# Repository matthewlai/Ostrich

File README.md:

# Ostrich
STM32F7 middleware library and development board.

# Size Notes
* Any std::istream/std::ostream instantiation (including including \<iostream\>) (~140KB)
* Floating point I/O support through libostrich streams (~10KB)
* Floating point scanf/printf support (~20KB)

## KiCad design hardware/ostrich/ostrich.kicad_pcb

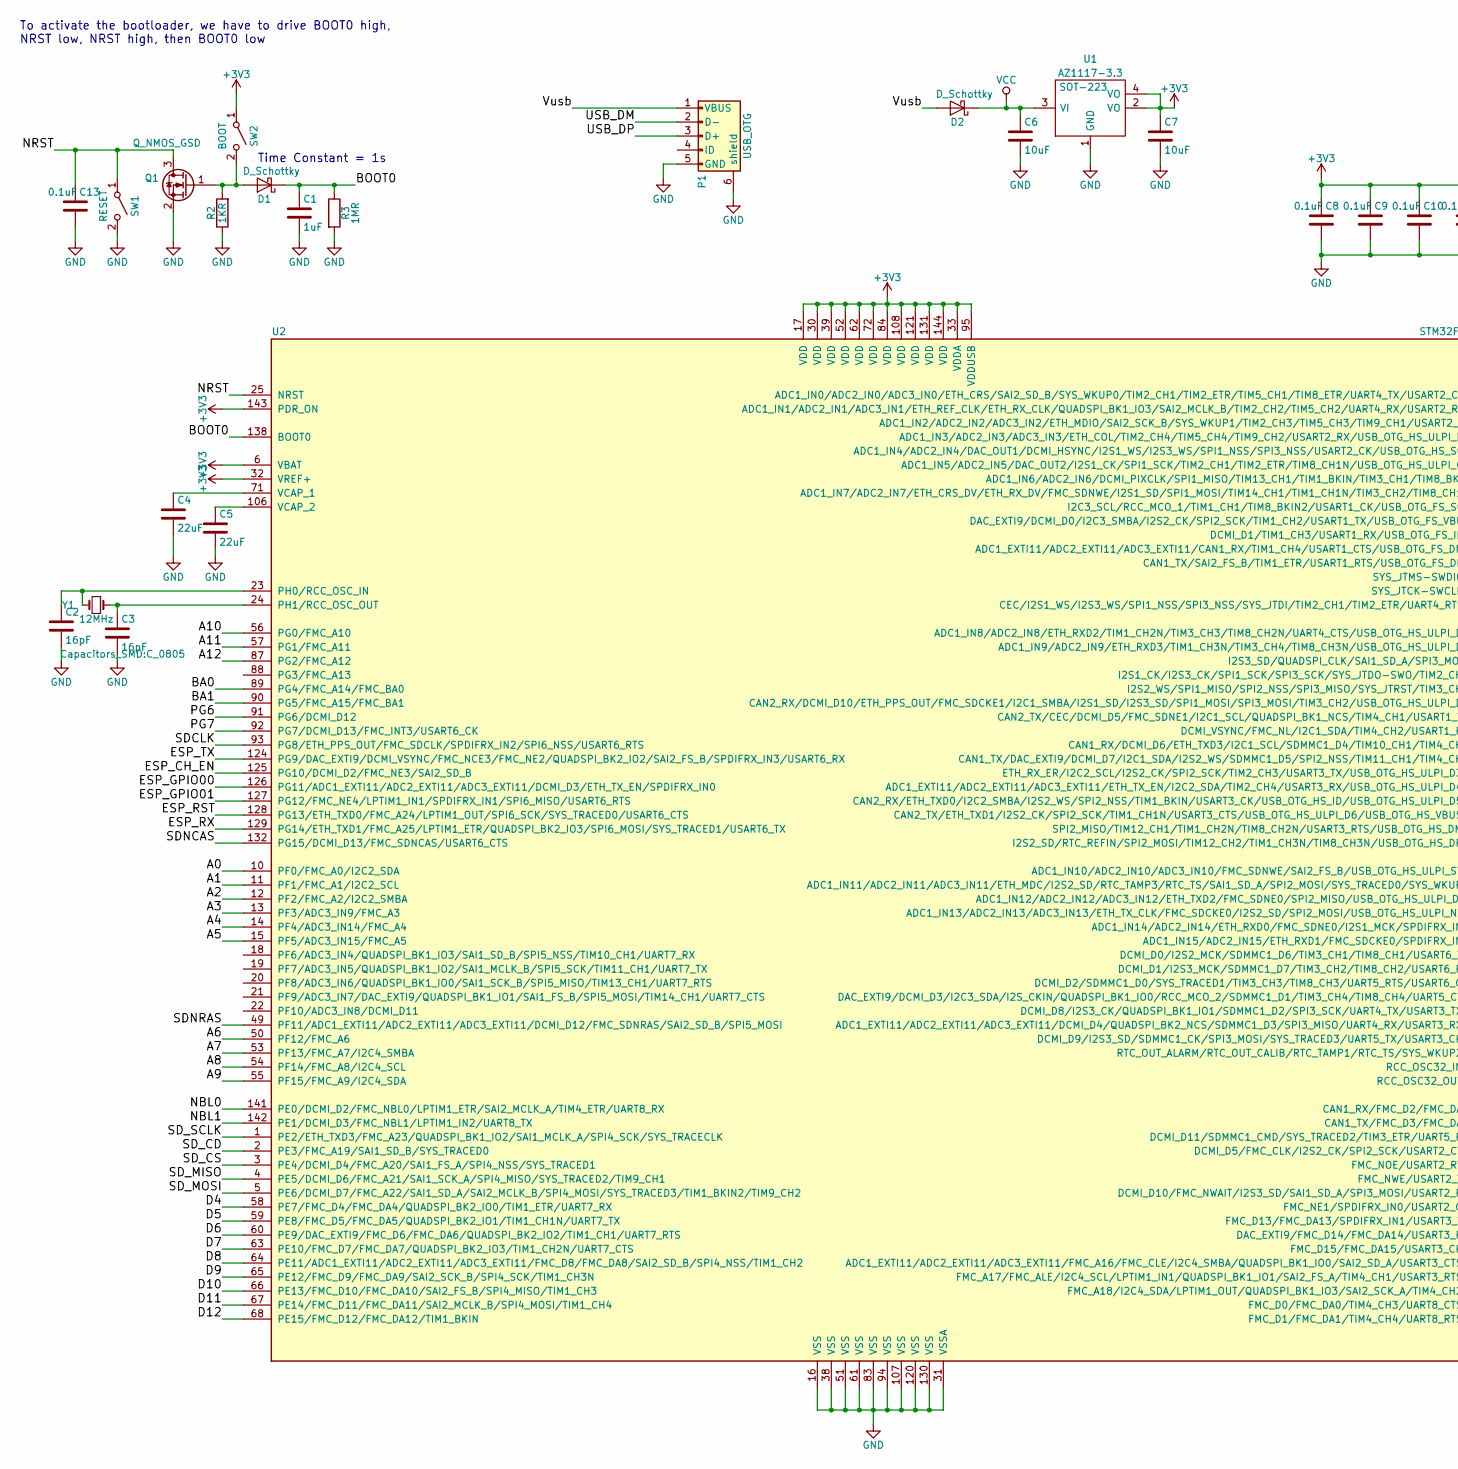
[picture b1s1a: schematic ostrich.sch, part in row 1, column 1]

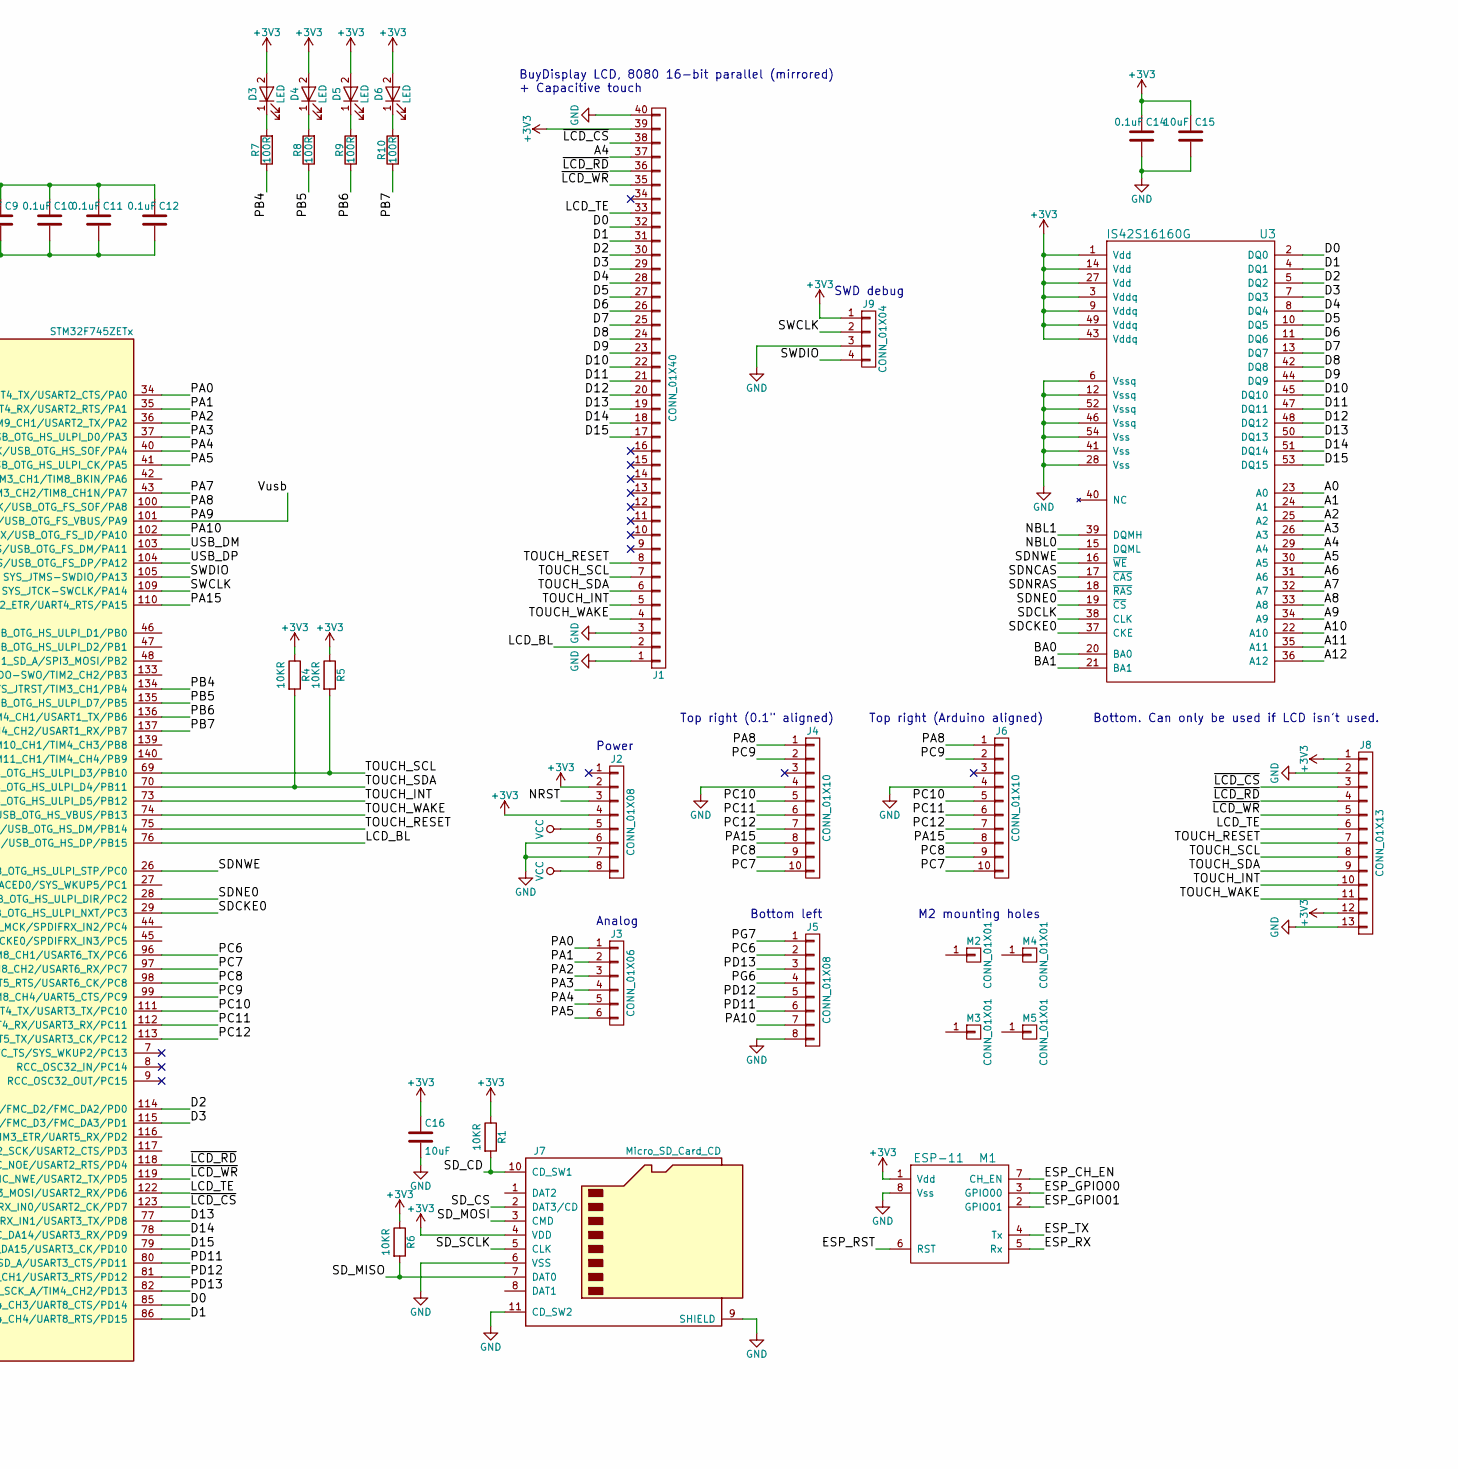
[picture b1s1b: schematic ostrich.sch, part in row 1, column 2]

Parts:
C1: 1uF; C_0805
C2, C3: 16pF; C_0805
C4, C5: 22uF; C_0805
C6, C7, C15, C16: 10uF; C_0805
C8, C9, C10, C11, C12, C13, C14: 0.1uF; C_0805
D1, D2: D_Schottky; D_1206
D3, D4, D5, D6: LED; LED_0805
J1: CONN_01X40; ER-CON40HB-2
J2, J5: CONN_01X08; Pin_Header_Straight_1x08_Pitch2.54mm
J3: CONN_01X06; Pin_Header_Straight_1x06_Pitch2.54mm
J4, J6: CONN_01X10; Pin_Header_Straight_1x10_Pitch2.54mm
J7: Micro_SD_Card_CD; Amphenol_1140084168
J8: CONN_01X13; Pin_Header_Straight_1x13_Pitch2.54mm
J9: CONN_01X04; Pin_Header_Straight_1x04_Pitch2.54mm
M1: ESP-11
M2, M3, M4, M5: CONN_01X01; M2_HOLE
P1: USB_OTG; USB_Micro-B_Molex_47346-0001_HS
Q1: Q_NMOS_GSD; SOT-23
R1, R4, R5, R6: 10KR; R_0805
R2: 1KR; R_0805
R3: 1MR; R_0805
R7, R8, R9, R10: 100R; R_0805
SW1: RESET; LL3301NF065QG
SW2: BOOT; LL3301NF065QG
U1: AZ1117-3.3; SOT-223
U2: STM32F745ZETx; LQFP-144_20x20mm_Pitch0.5mm
U3: IS42S16160G; TSOPII-54_10.16x22.22mm-Pitch0.8mm
Y1: 12MHz; Crystal_SMD_Abracon_ABM3-2pin_5.0x3.2mm_HandSoldering

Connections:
+3V3: C7.1, C8.1, C9.1, C10.1, C11.1, C12.1, C14.1, C15.1, C16.1, D3.2 (A), D4.2 (A), D5.2 (A), D6.2 (A), J1.39, J2.2, J2.4, J7.4 (VDD), J8.1, J8.12, J9.1, M1.1 (Vdd), R1.1, R4.1, R5.1, R6.1, SW2.1 (A), U1.2 (VO), U1.4 (VO), U2.6 (VBAT), U2.17 (VDD), U2.30 (VDD), U2.32 (VREF+), U2.33 (VDDA), U2.39 (VDD), U2.52 (VDD), U2.62 (VDD), U2.72 (VDD), U2.84 (VDD), U2.95 (VDDUSB), U2.108 (VDD), U2.121 (VDD), U2.131 (VDD), U2.143 (PDR_ON), U2.144 (VDD), U3.1 (Vdd), U3.3 (Vddq), U3.9 (Vddq), U3.14 (Vdd), U3.27 (Vdd), U3.43 (Vddq), U3.49 (Vddq)
/A0: U2.10 (PF0/FMC_A0/I2C2_SDA), U3.23 (A0)
/A1: U2.11 (PF1/FMC_A1/I2C2_SCL), U3.24 (A1)
/A2: U2.12 (PF2/FMC_A2/I2C2_SMBA), U3.25 (A2)
/A3: U2.13 (PF3/ADC3_IN9/FMC_A3), U3.26 (A3)
/A4: J1.37, U2.14 (PF4/ADC3_IN14/FMC_A4), U3.29 (A4)
/A5: U2.15 (PF5/ADC3_IN15/FMC_A5), U3.30 (A5)
/A6: U2.50 (PF12/FMC_A6), U3.31 (A6)
/A7: U2.53 (PF13/FMC_A7/I2C4_SMBA), U3.32 (A7)
/A8: U2.54 (PF14/FMC_A8/I2C4_SCL), U3.33 (A8)
/A9: U2.55 (PF15/FMC_A9/I2C4_SDA), U3.34 (A9)
/A10: U2.56 (PG0/FMC_A10), U3.22 (A10)
/A11: U2.57 (PG1/FMC_A11), U3.35 (A11)
/A12: U2.87 (PG2/FMC_A12), U3.36 (A12)
/BA0: U2.89 (PG4/FMC_A14/FMC_BA0), U3.20 (BA0)
/BA1: U2.90 (PG5/FMC_A15/FMC_BA1), U3.21 (BA1)
/BOOT0: C1.1, D1.1 (K), R3.1, U2.138 (BOOT0)
/D0: J1.32, U2.85 (FMC_D0/FMC_DA0/TIM4_CH3/UART8_CTS/PD14), U3.2 (DQ0)
/D1: J1.31, U2.86 (FMC_D1/FMC_DA1/TIM4_CH4/UART8_RTS/PD15), U3.4 (DQ1)
/D2: J1.30, U2.114 (CAN1_RX/FMC_D2/FMC_DA2/PD0), U3.5 (DQ2)
/D3: J1.29, U2.115 (CAN1_TX/FMC_D3/FMC_DA3/PD1), U3.7 (DQ3)
/D4: J1.28, U2.58 (PE7/FMC_D4/FMC_DA4/QUADSPI_BK2_IO0/TIM1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), U3.8 (DQ4)
/D5: J1.27, U2.59 (PE8/FMC_D5/FMC_DA5/QUADSPI_BK2_IO1/TIM1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), U3.10 (DQ5)
/D6: J1.26, U2.60 (PE9/DAC_EXTI9/FMC_D6/FMC_DA6/QUADSPI_BK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), U3.11 (DQ6)
/D7: J1.25, U2.63 (PE10/FMC_D7/FMC_DA7/QUADSPI_BK2_IO3/TIM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), U3.13 (DQ7)
/D8: J1.24, U2.64 (PE11/ADC1_EXTI11/ADC2_EXTI11/ADC3_EXTI1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), U3.42 (DQ8)
/D9: J1.23, U2.65 (PE12/FMC_D9/FMC_DA9/SAI2_SCK_B/SPI4_SCK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), U3.44 (DQ9)
/D10: J1.22, U2.66 (PE13/FMC_D10/FMC_DA10/SAI2_FS_B/SPI4_MI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), U3.45 (DQ10)
/D11: J1.21, U2.67 (PE14/FMC_D11/FMC_DA11/SAI2_MCLK_B/SPI4_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), U3.47 (DQ11)
/D12: J1.20, U2.68 (PE15/FMC_D12/FMC_DA12/TIM1_BKIN), U3.48 (DQ12)
/D13: J1.19, U2.77 (FMC_D13/FMC_DA13/SPDIFRX_IN1/USART3_TX/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), U3.50 (DQ13)
/D14: J1.18, U2.78 (DAC_EXTI9/FMC_D14/FMC_DA14/USART3_RX/PD9), U3.51 (DQ14)
/D15: J1.17, U2.79 (FMC_D15/FMC_DA15/USART3_CK/PD10), U3.53 (DQ15)
/ESP_CH_EN: M1.7 (CH_EN), U2.125 (PG10/DCMI_D2/FMC_NE3/SAI2_SD_B)
/ESP_GPIO00: M1.3 (GPIO00), U2.126 (PG11/ADC1_EXTI11/ADC2_EXTI11/ADC3_EXTI1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)
/ESP_GPIO01: M1.2 (GPIO01), U2.127 (PG12/FMC_NE4/LPTIM1_IN1/SPDIFRX_IN1/SPI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)
/ESP_RST: M1.6 (RST), U2.128 (PG13/ETH_TXD0/FMC_A24/LPTIM1_OUT/SPI6_S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)
/ESP_RX: M1.5 (Rx), U2.129 (PG14/ETH_TXD1/FMC_A25/LPTIM1_ETR/QUADSP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)
/ESP_TX: M1.4 (Tx), U2.124 (PG9/DAC_EXTI9/DCMI_VSYNC/FMC_NCE3/FMC_N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)
/LCD_BL: J1.2, U2.76 (I2S2_SD/RTC_REFIN/SPI2_MOSI/TIM12_CH2/T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)
/LCD_TE: J1.33, J8.6, U2.122 (DCMI_D10/FMC_NWAIT/I2S3_SD/SAI1_SD_A/SP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)
/NBL0: U2.141 (PE0/DCMI_D2/FMC_NBL0/LPTIM1_ETR/SAI2_MC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), U3.15 (DQML)
/NBL1: U2.142 (PE1/DCMI_D3/FMC_NBL1/LPTIM1_IN2/UART8_TX), U3.39 (DQMH)
/NRST: C13.1, J2.3, Q1.3 (D), SW1.1 (A), U2.25 (NRST)
/PA0: J3.1, U2.34 (ADC1_IN0/ADC2_IN0/ADC3_IN0/ETH_CRS/SAI2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)
/PA1: J3.2, U2.35 (ADC1_IN1/ADC2_IN1/ADC3_IN1/ETH_REF_CLK/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)
/PA2: J3.3, U2.36 (ADC1_IN2/ADC2_IN2/ADC3_IN2/ETH_MDIO/SAI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)
/PA3: J3.4, U2.37 (ADC1_IN3/ADC2_IN3/ADC3_IN3/ETH_COL/TIM2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)
/PA4: J3.5, U2.40 (ADC1_IN4/ADC2_IN4/DAC_OUT1/DCMI_HSYNC/I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)
/PA5: J3.6, U2.41 (ADC1_IN5/ADC2_IN5/DAC_OUT2/I2S1_CK/SPI1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)
/PA7: U2.43 (ADC1_IN7/ADC2_IN7/ETH_CRS_DV/ETH_RX_DV/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)
/PA8: J4.1, J6.1, U2.100 (I2C3_SCL/RCC_MCO_1/TIM1_CH1/TIM8_BKIN2/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)
/PA9: D2.2 (A), P1.1 (VBUS), U2.101 (DAC_EXTI9/DCMI_D0/I2C3_SMBA/I2S2_CK/SPI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)
/PA10: J5.7, U2.102 (DCMI_D1/TIM1_CH3/USART1_RX/USB_OTG_FS_I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)
/PA15: J4.8, J6.8, U2.110 (CEC/I2S1_WS/I2S3_WS/SPI1_NSS/SPI3_NSS/S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)
/PB4: R7.1, U2.134 (I2S2_WS/SPI1_MISO/SPI2_NSS/SPI3_MISO/SY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)
/PB5: R8.1, U2.135 (CAN2_RX/DCMI_D10/ETH_PPS_OUT/FMC_SDCKE1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)
/PB6: R9.1, U2.136 (CAN2_TX/CEC/DCMI_D5/FMC_SDNE1/I2C1_SCL/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)
/PB7: R10.1, U2.137 (DCMI_VSYNC/FMC_NL/I2C1_SDA/TIM4_CH2/USA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)
/PC6: J5.2, U2.96 (DCMI_D0/I2S2_MCK/SDMMC1_D6/TIM3_CH1/TIM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)
/PC7: J4.10, J6.10, U2.97 (DCMI_D1/I2S3_MCK/SDMMC1_D7/TIM3_CH2/TIM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)
/PC8: J4.9, J6.9, U2.98 (DCMI_D2/SDMMC1_D0/SYS_TRACED1/TIM3_CH3/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)
/PC9: J4.2, J6.2, U2.99 (DAC_EXTI9/DCMI_D3/I2C3_SDA/I2S_CKIN/QUA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)
/PC10: J4.5, J6.5, U2.111 (DCMI_D8/I2S3_CK/QUADSPI_BK1_IO1/SDMMC1_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)
/PC11: J4.6, J6.6, U2.112 (ADC1_EXTI11/ADC2_EXTI11/ADC3_EXTI11/DCM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)
/PC12: J4.7, J6.7, U2.113 (DCMI_D9/I2S3_SD/SDMMC1_CK/SPI3_MOSI/SYS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)
/PD11: J5.6, U2.80 (ADC1_EXTI11/ADC2_EXTI11/ADC3_EXTI11/FMC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)
/PD12: J5.5, U2.81 (FMC_A17/FMC_ALE/I2C4_SCL/LPTIM1_IN1/QUA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)
/PD13: J5.3, U2.82 (FMC_A18/I2C4_SDA/LPTIM1_OUT/QUADSPI_BK1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)
/PG6: J5.4, U2.91 (PG6/DCMI_D12)
/PG7: J5.1, U2.92 (PG7/DCMI_D13/FMC_INT3/USART6_CK)
/SDCKE0: U2.29 (ADC1_IN13/ADC2_IN13/ADC3_IN13/ETH_TX_CL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), U3.37 (CKE)
/SDCLK: U2.93 (PG8/ETH_PPS_OUT/FMC_SDCLK/SPDIFRX_IN2/S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), U3.38 (CLK)
/SDNCAS: U2.132 (PG15/DCMI_D13/FMC_SDNCAS/USART6_CTS), U3.17 (~CAS)
/SDNE0: U2.28 (ADC1_IN12/ADC2_IN12/ADC3_IN12/ETH_TXD2/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), U3.19 (~CS)
/SDNRAS: U2.49 (PF11/ADC1_EXTI11/ADC2_EXTI11/ADC3_EXTI1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), U3.18 (~RAS)
/SDNWE: U2.26 (ADC1_IN10/ADC2_IN10/ADC3_IN10/FMC_SDNWE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), U3.16 (~WE)
/SD_CD: J7.10 (CD_SW1), R1.2, U2.2 (PE3/FMC_A19/SAI1_SD_B/SYS_TRACED0)
/SD_CS: J7.2 (DAT3/CD), U2.3 (PE4/DCMI_D4/FMC_A20/SAI1_FS_A/SPI4_NSS/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)
/SD_MISO: J7.7 (DAT0), R6.2, U2.4 (PE5/DCMI_D6/FMC_A21/SAI1_SCK_A/SPI4_MIS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)
/SD_MOSI: J7.3 (CMD), U2.5 (PE6/DCMI_D7/FMC_A22/SAI1_SD_A/SAI2_MCLK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)
/SD_SCLK: J7.5 (CLK), U2.1 (PE2/ETH_TXD3/FMC_A23/QUADSPI_BK1_IO2/SA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)
/SWCLK: J9.2, U2.109 (SYS_JTCK-SWCLK/PA14)
/SWDIO: J9.4, U2.105 (SYS_JTMS-SWDIO/PA13)
/TOUCH_INT: J1.5, J8.10, U2.73 (CAN2_RX/ETH_TXD0/I2C2_SMBA/I2S2_WS/SPI2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)
/TOUCH_RESET: J1.8, J8.7, U2.75 (SPI2_MISO/TIM12_CH1/TIM1_CH2N/TIM8_CH2N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)
/TOUCH_SCL: J1.7, J8.8, R5.2, U2.69 (ETH_RX_ER/I2C2_SCL/I2S2_CK/SPI2_SCK/TIM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)
/TOUCH_SDA: J1.6, J8.9, R4.2, U2.70 (ADC1_EXTI11/ADC2_EXTI11/ADC3_EXTI11/ETH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)
/TOUCH_WAKE: J1.4, J8.11, U2.74 (CAN2_TX/ETH_TXD1/I2S2_CK/SPI2_SCK/TIM1_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)
/USB_DM: P1.2 (D-), U2.103 (ADC1_EXTI11/ADC2_EXTI11/ADC3_EXTI11/CAN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)
/USB_DP: P1.3 (D+), U2.104 (CAN1_TX/SAI2_FS_B/TIM1_ETR/USART1_RTS/U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)
/~LCD_CS: J1.38, J8.3, U2.123 (FMC_NE1/SPDIFRX_IN0/USART2_CK/PD7)
/~LCD_RD: J1.36, J8.4, U2.118 (FMC_NOE/USART2_RTS/PD4)
/~LCD_WR: J1.35, J8.5, U2.119 (FMC_NWE/USART2_TX/PD5)
GND: C1.2, C2.2, C3.2, C4.2, C5.2, C6.2, C7.2, C8.2, C9.2, C10.2, C11.2, C12.2, C13.2, C14.2, C15.2, C16.2, J1.1, J1.3, J1.40, J2.6, J2.7, J4.4, J5.8, J6.4, J7.6 (VSS), J7.9 (SHIELD), J7.11 (CD_SW2), J8.2, J8.13, J9.3, M1.8 (Vss), P1.5 (GND), P1.6 (shield), Q1.2 (S), R2.1, R3.2, SW1.2 (B), U1.1 (GND), U2.16 (VSS), U2.31 (VSSA), U2.38 (VSS), U2.51 (VSS), U2.61 (VSS), U2.83 (VSS), U2.94 (VSS), U2.107 (VSS), U2.120 (VSS), U2.130 (VSS), U3.6 (Vssq), U3.12 (Vssq), U3.28 (Vss), U3.41 (Vss), U3.46 (Vssq), U3.52 (Vssq), U3.54 (Vss)
unnamed: C2.1, U2.23 (PH0/RCC_OSC_IN), Y1.1
unnamed: C3.1, U2.24 (PH1/RCC_OSC_OUT), Y1.2
unnamed: C4.1, U2.71 (VCAP_1)
unnamed: C5.1, U2.106 (VCAP_2)
unnamed: D1.2 (A), Q1.1 (G), R2.2, SW2.2 (B)
unnamed: D3.1 (K), R7.2
unnamed: D4.1 (K), R8.2
unnamed: D5.1 (K), R9.2
unnamed: D6.1 (K), R10.2
VCC: C6.1, D2.1 (K), J2.5, J2.8, U1.3 (VI)

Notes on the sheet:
To activate the bootloader, we have to drive BOOT0 high, NRST low, NRST high, then BOOT0 low
Time Constant = 1s
BuyDisplay LCD, 8080 16-bit parallel (mirrored) + Capacitive touch
Analog
Power
Bottom. Can only be used if LCD isn't used.
Bottom left
Top right (0.1" aligned)
Top right (Arduino aligned)
SWD debug
M2 mounting holes

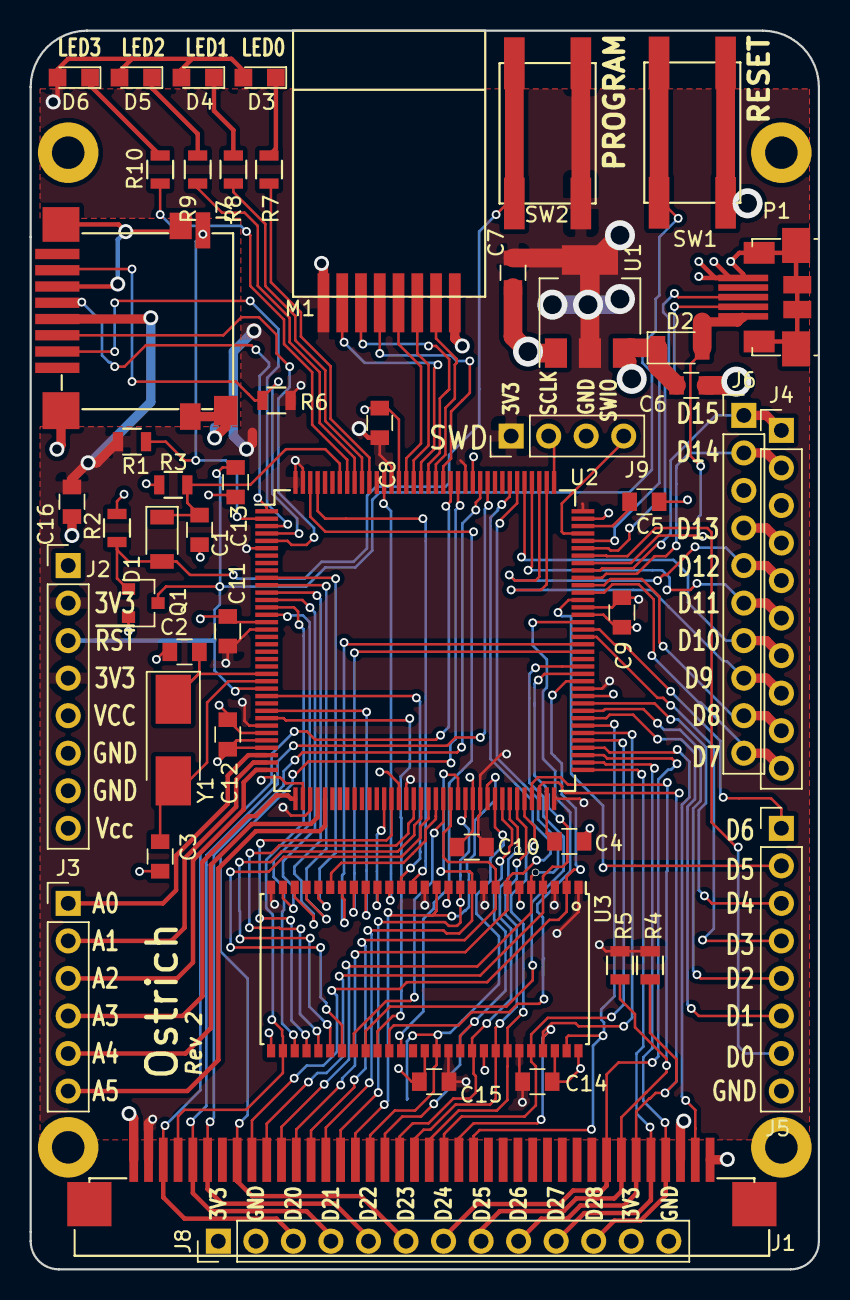
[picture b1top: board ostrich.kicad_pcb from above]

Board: 4 copper layers, 53.3 x 83.8 mm, 54 parts (0 on the bottom side), 104 nets.

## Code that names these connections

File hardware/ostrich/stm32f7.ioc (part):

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Mcu.Name=STM32F745Z(E-G)Tx
Mcu.Package=LQFP144
Mcu.UserName=STM32F745ZETx
PA0/WKUP.Signal=ADCx_IN0
PA1.Signal=ADCx_IN1
PA10.Mode=Asynchronous
PA10.Signal=USART1_RX
PA11.Mode=Device_Only
PA11.Signal=USB_OTG_FS_DM
PA12.Mode=Device_Only
PA12.Signal=USB_OTG_FS_DP
PA13.Signal=SYS_JTMS-SWDIO
PA14.Signal=SYS_JTCK-SWCLK
PA15.Mode=NSS_Signal_Hard_Output
PA15.Signal=SPI3_NSS
PA2.Signal=ADCx_IN2
PA3.Signal=ADCx_IN3
PA4.Signal=ADCx_IN4
PA5.Signal=ADCx_IN5
PA8.Mode=I2C
PA8.Signal=I2C3_SCL
PA9.Mode=Asynchronous
PA9.Signal=USART1_TX
PB10.Mode=Asynchronous
PB10.Signal=USART3_TX
PB11.Mode=Asynchronous
PB11.Signal=USART3_RX
PB12.Signal=GPXTI12
PB13.Signal=GPIO_Output
PB14.Signal=GPIO_Output
PB15.Signal=S_TIM12_CH2
PB4.Signal=GPIO_Output
PB5.Signal=GPIO_Output
PB6.Signal=GPIO_Output
PB7.Signal=GPIO_Output
PC0.Signal=FMC_SDNWE
PC10.Mode=Full_Duplex_Master
PC10.Signal=SPI3_SCK
PC11.Mode=Full_Duplex_Master
PC11.Signal=SPI3_MISO
PC12.Mode=Full_Duplex_Master
PC12.Signal=SPI3_MOSI
PC2.Mode=SdramChipSelect1_1
PC2.Signal=FMC_SDNE0
PC3.Mode=SdramChipSelect1_1
PC3.Signal=FMC_SDCKE0
PC6.Signal=S_TIM3_CH1
PC7.Signal=S_TIM3_CH2
PC8.Signal=S_TIM3_CH3
PC9.Mode=I2C
PC9.Signal=I2C3_SDA
PD0.Signal=FMC_D2_DA2
PD1.Signal=FMC_D3_DA3
PD10.Signal=FMC_D15_DA15
PD11.Signal=GPIO_Output
PD12.Signal=S_TIM4_CH1
PD13.Signal=S_TIM4_CH2
PD14.Signal=FMC_D0_DA0
PD15.Signal=FMC_D1_DA1
PD8.Signal=FMC_D13_DA13
PD9.Signal=FMC_D14_DA14
PE0.Signal=FMC_NBL0
PE1.Signal=FMC_NBL1
PE10.Signal=FMC_D7_DA7
PE11.Signal=FMC_D8_DA8
PE12.Signal=FMC_D9_DA9
PE13.Signal=FMC_D10_DA10
PE14.Signal=FMC_D11_DA11
PE15.Signal=FMC_D12_DA12
PE2.Mode=Full_Duplex_Master
PE2.Signal=SPI4_SCK
PE4.Mode=NSS_Signal_Hard_Output
PE4.Signal=SPI4_NSS
PE5.Mode=Full_Duplex_Master
PE5.Signal=SPI4_MISO
PE6.Mode=Full_Duplex_Master
PE6.Signal=SPI4_MOSI
PE7.Signal=FMC_D4_DA4
PE8.Signal=FMC_D5_DA5
PE9.Signal=FMC_D6_DA6
PF0.Signal=FMC_A0
PF1.Signal=FMC_A1
PF11.Signal=FMC_SDNRAS
PF12.Signal=FMC_A6
PF13.Signal=FMC_A7
PF14.Signal=FMC_A8
PF15.Signal=FMC_A9
PF2.Signal=FMC_A2
PF3.Signal=FMC_A3
PF4.Signal=FMC_A4
PF5.Signal=FMC_A5
PG0.Signal=FMC_A10
PG1.Signal=FMC_A11
PG14.Mode=Asynchronous
PG14.Signal=USART6_TX
PG15.Signal=FMC_SDNCAS
PG2.Signal=FMC_A12
PG4.Signal=FMC_A14_BA0
PG5.Signal=FMC_A15_BA1
PG6.Signal=GPIO_Output
PG7.Signal=GPIO_Output
PG8.Signal=FMC_SDCLK
PG9.Mode=Asynchronous
PG9.Signal=USART6_RX
PH0/OSC_IN.Mode=HSE-External-Oscillator
PH0/OSC_IN.Signal=RCC_OSC_IN
PH1/OSC_OUT.Mode=HSE-External-Oscillator
PH1/OSC_OUT.Signal=RCC_OSC_OUT
RCC.HSE_VALUE=12000000
RCC.SYSCLKFreq_VALUE=216000000
RCC.SYSCLKSource=RCC_SYSCLKSOURCE_PLLCLK

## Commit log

2017-02-26 Added *.o and *.d to ignore
2017-02-26 Added docs
2017-02-26 Added kicad backup files to .gitignore, and first rev board design
2017-02-26 Added libopencm3 submodule
2017-02-27 Added stm32f7 makefile
2017-03-01 Removed an autosaved file
2017-03-01 Updated libopencm3
2017-03-02 Added Makefiles
2017-03-02 Fixed Makefile.stm32f7 include path
2017-03-02 Updated Makefile rules and a WIP example project
2017-03-02 Fixed Makefile capitalization
2017-03-02 Added libostrich and tweaked makefiles
2017-04-17 Added pin assignments
2017-04-21 Added sublime workspace file to gitignore
2017-04-21 Added script for flashing using st-link
2017-04-21 Added Sublime project file
2017-04-21 Fixed rules.mk formatting
2017-04-26 Fixed Makefile to not use__cxa_atexit and guards around static initializers
2017-04-27 Updated blink example
2017-04-27 Added basic GPIO support
2017-04-27 Converted to Google C++ style... more or less. No functional change.
2018-07-15 Update libopencm3
2018-07-16 Moved Gpio pin definitions into Gpio namespace, and deleted generation script
2018-07-23 Updated makefile for compatibility with GCC 7, reverted GPIO defs namespace change
2018-08-15 Added GPIO input support
2018-08-15 Added sublime project
2018-08-15 Added Cortex M7 Technical Reference Manual
2018-08-15 Added ARMv7-M Architecture Reference Manual
2018-08-15 Updated sublime project
2018-08-15 Added system initialization
2018-08-16 Added systick support
2018-08-16 Updated blink example to use systick
2018-08-29 Added CDC-ACM (USB Serial)
2018-08-29 Added USB configuration options to CDC-ACM constructor
2018-08-29 Added script to flash through DFU
2018-08-29 Fixed SD slot orientation and diode footprint
2018-08-29 Added USB serial echo example
2018-08-29 Fixed indentation
2019-04-28 Updated libopencm3 from upstream
2019-05-12 ADC WIP
2019-05-12 Added empty directory for obj/usb
2019-05-12 Added Vbus and rearranged digital pins
2019-05-12 Implemented SingleConversion ADC
2019-05-12 Updated example board configs
2019-05-12 Added float printing support
2019-05-12 Added turning ADC on, and fixed sample time handlign
2019-05-12 Updated libopencm3 for the USB revert fix
2019-05-12 More ADC sampling time fixing
2019-05-12 Added busy waiting functions
2019-05-12 Fixed ADC bugs and added temperature reading
2019-05-12 Added ADC example
2019-05-13 Fixed missing namespace
2019-05-14 Added missing namespace
2019-05-14 Added USART WIP
2019-05-16 Silence GCC warnings about an ABI conformance bug introduced in GCC 5 and fixed in GCC 7.1 (https://gcc.gnu.org/gcc-7/changes.html)
2019-05-18 Switched USB serial from std::iostream to our own stream implementation for space (std::iostream uses about 140KB)
2019-05-18 Moved comments
2019-05-18 Updated comment
2019-05-18 USART WIP
2019-05-19 Updated usb_serial_echo example to use new Buffered*Stream API
2019-05-19 Added alias for UnbufferedOutputStream
2019-05-20 Fixed USART ISR linking
2019-05-20 Added raw read/write functions to Buffered*Stream
2019-05-20 Added logging handler
2019-05-20 Implemented USART stream
2019-05-20 Added OpenOCD scripts
2019-05-20 Added usart<=>USB serial adapter example
2019-05-20 Updated footprint table for KiCad 5, removed 0.1 inch aligned connector, and added all SWD pins
2019-05-25 Added ESP8266 flashing script
2019-05-25 Added check for error and logging handlers before calling them
2019-05-25 Added USB baud rate setting and proper traffic control
2019-05-25 Added interface to support buffer management in BufferedInputStream
2019-05-25 Removed dead code
2019-05-25 Support baud rate changing in serial UART example
2019-05-25 Added example for flashing ESP8266 with our MCU as adapter
2019-05-25 Removed GpioDef namespace, and changed examples to import Ostrich namespace
2019-05-25 Simplifed GPIO defs and changed PIN_INVALID definition
2019-05-25 Changed GPIO allocation to be RAII
2019-05-25 Switched to C++17
2019-05-25 Changed blink example to use standard DelayMilliseconds()
2019-05-26 Added basic synchronous I2C support
2019-05-26 Added i2c_usb_moisture example
2019-05-26 Added missing update
2019-06-05 Added I2C4 pin option, USB serial not send if port not opened, GPIO OutputPin set option, StringStream class, examples
2019-06-07 Better I2C timeout handling
2019-09-25 Fixed overflow handling in integer formatting
2019-09-25 Fixed integer formatting
2019-09-27 Updated comments
